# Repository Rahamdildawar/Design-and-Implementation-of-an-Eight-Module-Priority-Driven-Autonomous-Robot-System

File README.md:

# 🤖 Eight-Module Priority-Driven Autonomous Robot System

**Design and Implementation of an Eight-Module Priority-Driven Autonomous Robot System with Integrated Computer Vision and Multi-Sensor Fusion**

Author: **Raham Dil** — Computer Engineering, Ghulam Ishaq Khan Institute of Engineering Sciences and Technology (GIKI)
📧 u2024529@giki.edu.pk

<p align="center">
  <em>Platform: Arduino Mega 2560 + Python/OpenCV vision subsystem</em>
</p>

---

## 📖 Overview

This project presents a comprehensive **autonomous robot platform** built on the **Arduino Mega 2560**, augmented with a **laptop-based computer vision subsystem** written in **Python 3.9+ / OpenCV**. Eight independent hardware and software modules are unified under a **deterministic, five-level priority engine** that guarantees safe, predictable arbitration whenever multiple sensor events occur simultaneously (e.g., smoke detection + manual override + obstacle in path).

The system was validated experimentally, achieving **100% correct priority arbitration** across all tested concurrent-hazard scenarios.

---

## ✨ Key Contributions

- A **five-level priority engine** that deterministically arbitrates eight heterogeneous sensor-actuator modules in real time.
- An integrated **computer vision pipeline** (pothole detection, face dataset collection, gesture navigation zone) communicating with the embedded controller over a lightweight serial protocol.
- A **modular firmware/software architecture** enabling independent development and testing of each module while preserving system-wide safety invariants.
- **Empirical validation** of the priority engine under concurrent hazard conditions, with quantitative performance metrics.

---

## 🧩 System Modules

<table>
  <thead>
    <tr>
      <th align="center">#</th>
      <th align="left">Module</th>
      <th align="left">Description</th>
    </tr>
  </thead>
  <tbody>
    <tr>
      <td align="center">1</td>
      <td><strong>Smoke &amp; Gas Detection</strong></td>
      <td>3× MQ-series gas sensors (L/C/R) — highest priority safety shutdown</td>
    </tr>
    <tr>
      <td align="center">2</td>
      <td><strong>Pothole Detection (CV)</strong></td>
      <td>OpenCV pipeline: Gaussian blur → Canny edges → contour/circularity filtering</td>
    </tr>
    <tr>
      <td align="center">3</td>
      <td><strong>Flame Tracking &amp; Suppression</strong></td>
      <td>3× KY-026 IR flame sensors, 2-stage track-then-suppress logic with fan actuator</td>
    </tr>
    <tr>
      <td align="center">4</td>
      <td><strong>Ultrasonic Obstacle Avoidance</strong></td>
      <td>3× HC-SR04 sensors, reverse–scan–turn maneuver below 18 cm</td>
    </tr>
    <tr>
      <td align="center">5</td>
      <td><strong>Face Dataset Collection</strong></td>
      <td>Viola–Jones (Haar cascade) face capture pipeline for downstream recognition training</td>
    </tr>
    <tr>
      <td align="center">6</td>
      <td><strong>Finger Gesture Control</strong></td>
      <td>ROI-based gesture navigation zone (ready for MediaPipe Hands integration)</td>
    </tr>
    <tr>
      <td align="center">7</td>
      <td><strong>Bluetooth Teleoperation</strong></td>
      <td>HC-05 module on <code>Serial1</code>, ASCII motion + speed protocol</td>
    </tr>
    <tr>
      <td align="center">8</td>
      <td><strong>Infrared Line Following</strong></td>
      <td>5× TCRT5000 sensors, rule-based sensor-to-action mapping (default behavior)</td>
    </tr>
  </tbody>
</table>

<p align="center"><em>Representative component images (5-ch IR array, HC-SR04, L298N driver) — not the project's own hardware photos.</em></p>

---

## 🏗️ System Architecture

The software stack is split into two tiers:

- **Embedded tier (C++/Arduino):** Runs at ~200 Hz on the Mega 2560. Implements the priority engine, all sensor drivers, and motor control primitives.
- **Vision tier (Python 3.9+):** Runs on a connected laptop at ~25–30 FPS. Implements Modules 2, 5, and 6 via OpenCV, sending single-byte ASCII decisions to the embedded tier over USB serial.

```
┌─────────────────────────┐        USB Serial (9600 baud)        ┌──────────────────────────┐
│   Python Vision Tier     │ ────────────────────────────────────▶│   Arduino Mega 2560       │
│  (OpenCV, 25–30 FPS)     │   ASCII tokens: P, C, F, B, L, R, S   │  Priority Engine (~200Hz) │
│  • Pothole Detection     │◀──────────────────────────────────── │  • 8 Modules              │
│  • Face Collector        │                                       │  • Motor Control (L298N)  │
│  • Gesture Zone          │                                       └──────────────┬───────────┘
└─────────────────────────┘                                                       │ Serial1 (9600 baud)
                                                                                    ▼
                                                                        ┌──────────────────────┐
                                                                        │   HC-05 Bluetooth     │
                                                                        │   (Teleoperation)     │
                                                                        └──────────────────────┘
```

### Priority Hierarchy

<table>
  <thead>
    <tr>
      <th align="center">Priority</th>
      <th align="left">Condition</th>
      <th align="center">Modules</th>
      <th align="left">Action</th>
    </tr>
  </thead>
  <tbody>
    <tr>
      <td align="center"><strong>1 (highest)</strong></td>
      <td>Smoke OR pothole brake</td>
      <td align="center">1, 2</td>
      <td>Stop motors, buzzer ON, return</td>
    </tr>
    <tr>
      <td align="center"><strong>2</strong></td>
      <td>Flame detected</td>
      <td align="center">3</td>
      <td>Track &amp; suppress, return</td>
    </tr>
    <tr>
      <td align="center"><strong>3</strong></td>
      <td>Front obstacle &lt; 18 cm</td>
      <td align="center">4</td>
      <td>Reverse, scan, turn, return</td>
    </tr>
    <tr>
      <td align="center"><strong>4</strong></td>
      <td>Manual command within 700 ms</td>
      <td align="center">5, 6, 7</td>
      <td>Execute motion command, return</td>
    </tr>
    <tr>
      <td align="center"><strong>5 (default)</strong></td>
      <td>—</td>
      <td align="center">8</td>
      <td>Line following</td>
    </tr>
  </tbody>
</table>

Each level acts as a guard: if satisfied, all lower levels are bypassed via an early `return`, guaranteeing mutually exclusive behavior within a single control loop iteration.

---

## 🔌 Serial Communication Protocol

<table>
  <thead>
    <tr>
      <th align="center">Token</th>
      <th align="center">Direction</th>
      <th align="left">Meaning</th>
    </tr>
  </thead>
  <tbody>
    <tr><td align="center"><code>P</code></td><td align="center">PC → Mega</td><td>Pothole/hazard detected — halt</td></tr>
    <tr><td align="center"><code>C</code></td><td align="center">PC → Mega</td><td>Pothole cleared — resume</td></tr>
    <tr><td align="center"><code>F</code></td><td align="center">PC/BT → Mega</td><td>Move forward</td></tr>
    <tr><td align="center"><code>B</code></td><td align="center">PC/BT → Mega</td><td>Move backward</td></tr>
    <tr><td align="center"><code>L</code></td><td align="center">PC/BT → Mega</td><td>Pivot left</td></tr>
    <tr><td align="center"><code>R</code></td><td align="center">PC/BT → Mega</td><td>Pivot right</td></tr>
    <tr><td align="center"><code>S</code></td><td align="center">PC/BT → Mega</td><td>Stop motors</td></tr>
    <tr><td align="center"><code>0</code>–<code>9</code></td><td align="center">BT → Mega</td><td>Set speed (mapped 0–255)</td></tr>
  </tbody>
</table>

---

## 🛠️ Hardware / Pin Assignments (Arduino Mega 2560)

<table>
  <thead>
    <tr>
      <th align="left">Module</th>
      <th align="left">Signal</th>
      <th align="center">Pin</th>
      <th align="center">Direction</th>
    </tr>
  </thead>
  <tbody>
    <tr><td>Motor Driver</td><td>ENA / IN1 / IN2 / IN3 / IN4 / ENB</td><td align="center">2 / 3 / 4 / 7 / 8 / 5</td><td align="center">OUT</td></tr>
    <tr><td>Module 8 (Line)</td><td>S1–S5</td><td align="center">22–26</td><td align="center">IN</td></tr>
    <tr><td>Module 3 (Flame)</td><td>FL, FC, FR</td><td align="center">30–32</td><td align="center">IN</td></tr>
    <tr><td>Module 1 (Smoke)</td><td>SL, SC, SR</td><td align="center">35–37</td><td align="center">IN</td></tr>
    <tr><td>Module 4 (Ultrasonic)</td><td>TRIG/ECHO × 3</td><td align="center">40–45</td><td align="center">OUT/IN</td></tr>
    <tr><td>Actuators</td><td>FAN / BUZZER</td><td align="center">9 / 10</td><td align="center">OUT</td></tr>
  </tbody>
</table>

> Full wiring schematics, PCB layout (2D & 3D), and simulation screenshots (flame/smoke, line follower, Bluetooth, full-integration) are available in [`/docs/circuit-diagrams`](./docs/circuit-diagrams) — see the original report's Figure 2 set.

---

## 💻 Software Structure

**Embedded Firmware (`/firmware`)**
```
firmware/
├── main.ino                  # setup(), main priority-engine loop
├── serial_handler.cpp        # readControlInputs()
├── ultrasonic.cpp            # getDistance()
├── line_follower.cpp         # runLineFollowingRoutine()
├── manual_dispatch.cpp       # executeManualAction()
└── motor_primitives.cpp      # forward(), backward(), pivotLeft/Right(), stopMotors()
```

**Vision System (`/vision`)**
```
vision/
├── config.py           # Config dataclass — tunable parameters
├── serial_manager.py   # SerialManager — pyserial wrapper w/ simulation fallback
├── obstacle_detector.py# ObstacleDetector — Module 2 (pothole detection)
├── face_collector.py   # FaceCollector — Module 5
├── gesture_zone.py     # GestureZone — Module 6 ROI overlay/accessor
├── hud.py              # HUD — on-screen status bar
└── main.py             # Entry point / frame processing loop
```

---

## 🚀 Getting Started

### Prerequisites
- Arduino IDE (or PlatformIO)
- Python 3.9+
- `opencv-python`, `pyserial` (`pip install opencv-python pyserial`)
- Arduino Mega 2560, L298N driver, HC-SR04 ×3, KY-026 ×3, MQ-series gas sensors ×3, TCRT5000 ×5, HC-05

### 1. Flash the firmware
```bash
# Open firmware/main.ino in Arduino IDE, select "Arduino Mega 2560", and upload
```

### 2. Run the vision system
```bash
cd vision
python main.py --port COM5 --baud 9600   # adjust port for your OS
```

### 3. Control the robot
- **Autonomous:** line following runs by default; hazards auto-preempt.
- **Manual (Bluetooth/keyboard):** send `F`, `B`, `L`, `R`, `S`, or a digit `0`–`9` for speed.

---

## 📊 Experimental Results

### Priority Engine Arbitration (20 trials/scenario)

<table>
  <thead>
    <tr>
      <th align="left">Scenario</th>
      <th align="center">Expected</th>
      <th align="center">Observed</th>
      <th align="center">Accuracy</th>
    </tr>
  </thead>
  <tbody>
    <tr><td>Smoke only</td><td align="center">Stop+Buzz</td><td align="center">Stop+Buzz</td><td align="center">100%</td></tr>
    <tr><td>Flame only</td><td align="center">Track+Fan</td><td align="center">Track+Fan</td><td align="center">100%</td></tr>
    <tr><td>Obstacle only</td><td align="center">Avoid</td><td align="center">Avoid</td><td align="center">100%</td></tr>
    <tr><td>Smoke + Flame</td><td align="center">Stop+Buzz</td><td align="center">Stop+Buzz</td><td align="center">100%</td></tr>
    <tr><td>Smoke + Manual</td><td align="center">Stop+Buzz</td><td align="center">Stop+Buzz</td><td align="center">100%</td></tr>
    <tr><td>Flame + Manual</td><td align="center">Track+Fan</td><td align="center">Track+Fan</td><td align="center">100%</td></tr>
    <tr><td>Pothole (CV) + Manual</td><td align="center">Stop</td><td align="center">Stop</td><td align="center">100%</td></tr>
    <tr><td>All hazards active</td><td align="center">Stop+Buzz</td><td align="center">Stop+Buzz</td><td align="center">100%</td></tr>
  </tbody>
</table>

100% correct arbitration was observed across all 8 concurrent hazard scenarios.

### Pothole Detection (Module 2) — Confusion Matrix (200-frame test set)

<table>
  <thead>
    <tr>
      <th></th>
      <th align="center">Predicted: Pothole</th>
      <th align="center">Predicted: Clear</th>
      <th align="center">Total</th>
    </tr>
  </thead>
  <tbody>
    <tr><td><strong>Actual: Pothole</strong></td><td align="center">88</td><td align="center">12</td><td align="center">100</td></tr>
    <tr><td><strong>Actual: Clear</strong></td><td align="center">9</td><td align="center">91</td><td align="center">100</td></tr>
    <tr><td><strong>Total</strong></td><td align="center">97</td><td align="center">103</td><td align="center">200</td></tr>
  </tbody>
</table>

<table>
  <thead>
    <tr><th align="left">Metric</th><th align="center">Value</th></tr>
  </thead>
  <tbody>
    <tr><td>Precision</td><td align="center">90.7%</td></tr>
    <tr><td>Recall</td><td align="center">88.0%</td></tr>
    <tr><td>F1-Score</td><td align="center">0.894</td></tr>
  </tbody>
</table>

### Obstacle Avoidance (Module 4) — Threshold 18 cm

<table>
  <thead>
    <tr>
      <th align="center">Distance (cm)</th>
      <th align="center">Trials</th>
      <th align="center">Detected</th>
      <th align="center">Avoided</th>
      <th align="center">Accuracy</th>
    </tr>
  </thead>
  <tbody>
    <tr><td align="center">10</td><td align="center">10</td><td align="center">10</td><td align="center">10</td><td align="center">100%</td></tr>
    <tr><td align="center">15</td><td align="center">10</td><td align="center">10</td><td align="center">10</td><td align="center">100%</td></tr>
    <tr><td align="center">20</td><td align="center">10</td><td align="center">0</td><td align="center">0</td><td align="center">N/A</td></tr>
    <tr><td align="center">25</td><td align="center">10</td><td align="center">0</td><td align="center">0</td><td align="center">N/A</td></tr>
  </tbody>
</table>

### Line Following (Module 8)

<table>
  <thead>
    <tr>
      <th align="left">Track Type</th>
      <th align="center">Laps</th>
      <th align="center">Completed</th>
      <th align="center">Rate</th>
    </tr>
  </thead>
  <tbody>
    <tr><td>Straight</td><td align="center">10</td><td align="center">10</td><td align="center">100%</td></tr>
    <tr><td>Gentle curve (15°)</td><td align="center">10</td><td align="center">10</td><td align="center">100%</td></tr>
    <tr><td>Sharp curve (45°)</td><td align="center">10</td><td align="center">8</td><td align="center">80%</td></tr>
  </tbody>
</table>

### End-to-End Latency (Pothole Detection → Motor Stop, 50 trials)

<table>
  <thead>
    <tr><th align="left">Metric</th><th align="center">Value</th></tr>
  </thead>
  <tbody>
    <tr><td>Mean latency</td><td align="center">48.3 ms</td></tr>
    <tr><td>Standard deviation</td><td align="center">6.1 ms</td></tr>
    <tr><td>Maximum latency</td><td align="center">62 ms</td></tr>
  </tbody>
</table>

Dominant cost: USB-UART transmission at 9600 baud + camera frame period (~33 ms at 30 fps).

---

## ⚠️ Known Limitations

- **Blocking delays** in flame suppression (2 s) and obstacle avoidance (350/500 ms) pause serial processing — future work: interrupt/timer-driven non-blocking control.
- **Pothole detector** (classical CV) is sensitive to lighting; a lightweight CNN (e.g., MobileNetV2) is recommended for outdoor robustness.
- **Gesture recognition (Module 6)** currently only renders the ROI — classifier (e.g., MediaPipe Hands) not yet implemented.
- **Serial protocol** has no checksum/error correction; a lightweight XOR checksum is a suggested improvement.

---

## 🔭 Future Work

- Replace blocking delays with timer-interrupt–based non-blocking suppression/avoidance routines.
- Integrate a CNN-based pothole detector.
- Implement the Module 6 gesture classifier (MediaPipe Hands or custom CNN).
- Add a lightweight serial error-detection/checksum scheme.
- Increase baud rate to 115200 to reduce end-to-end latency.

---

## 📚 References

Key references include Brooks' subsumption architecture, Arkin's motor-schema navigation, Siegwart & Nourbakhsh's *Introduction to Autonomous Mobile Robots*, Viola & Jones' cascade face detector, and ROS (Quigley et al.). See the full report for the complete bibliography.

---

## 🙏 Acknowledgment

Thanks to the Department of Electrical Engineering (GIKI) for providing laboratory facilities and hardware components used in this project.

---

## 📄 License

This project is released for educational and research purposes. Add your preferred license (e.g., MIT) here.

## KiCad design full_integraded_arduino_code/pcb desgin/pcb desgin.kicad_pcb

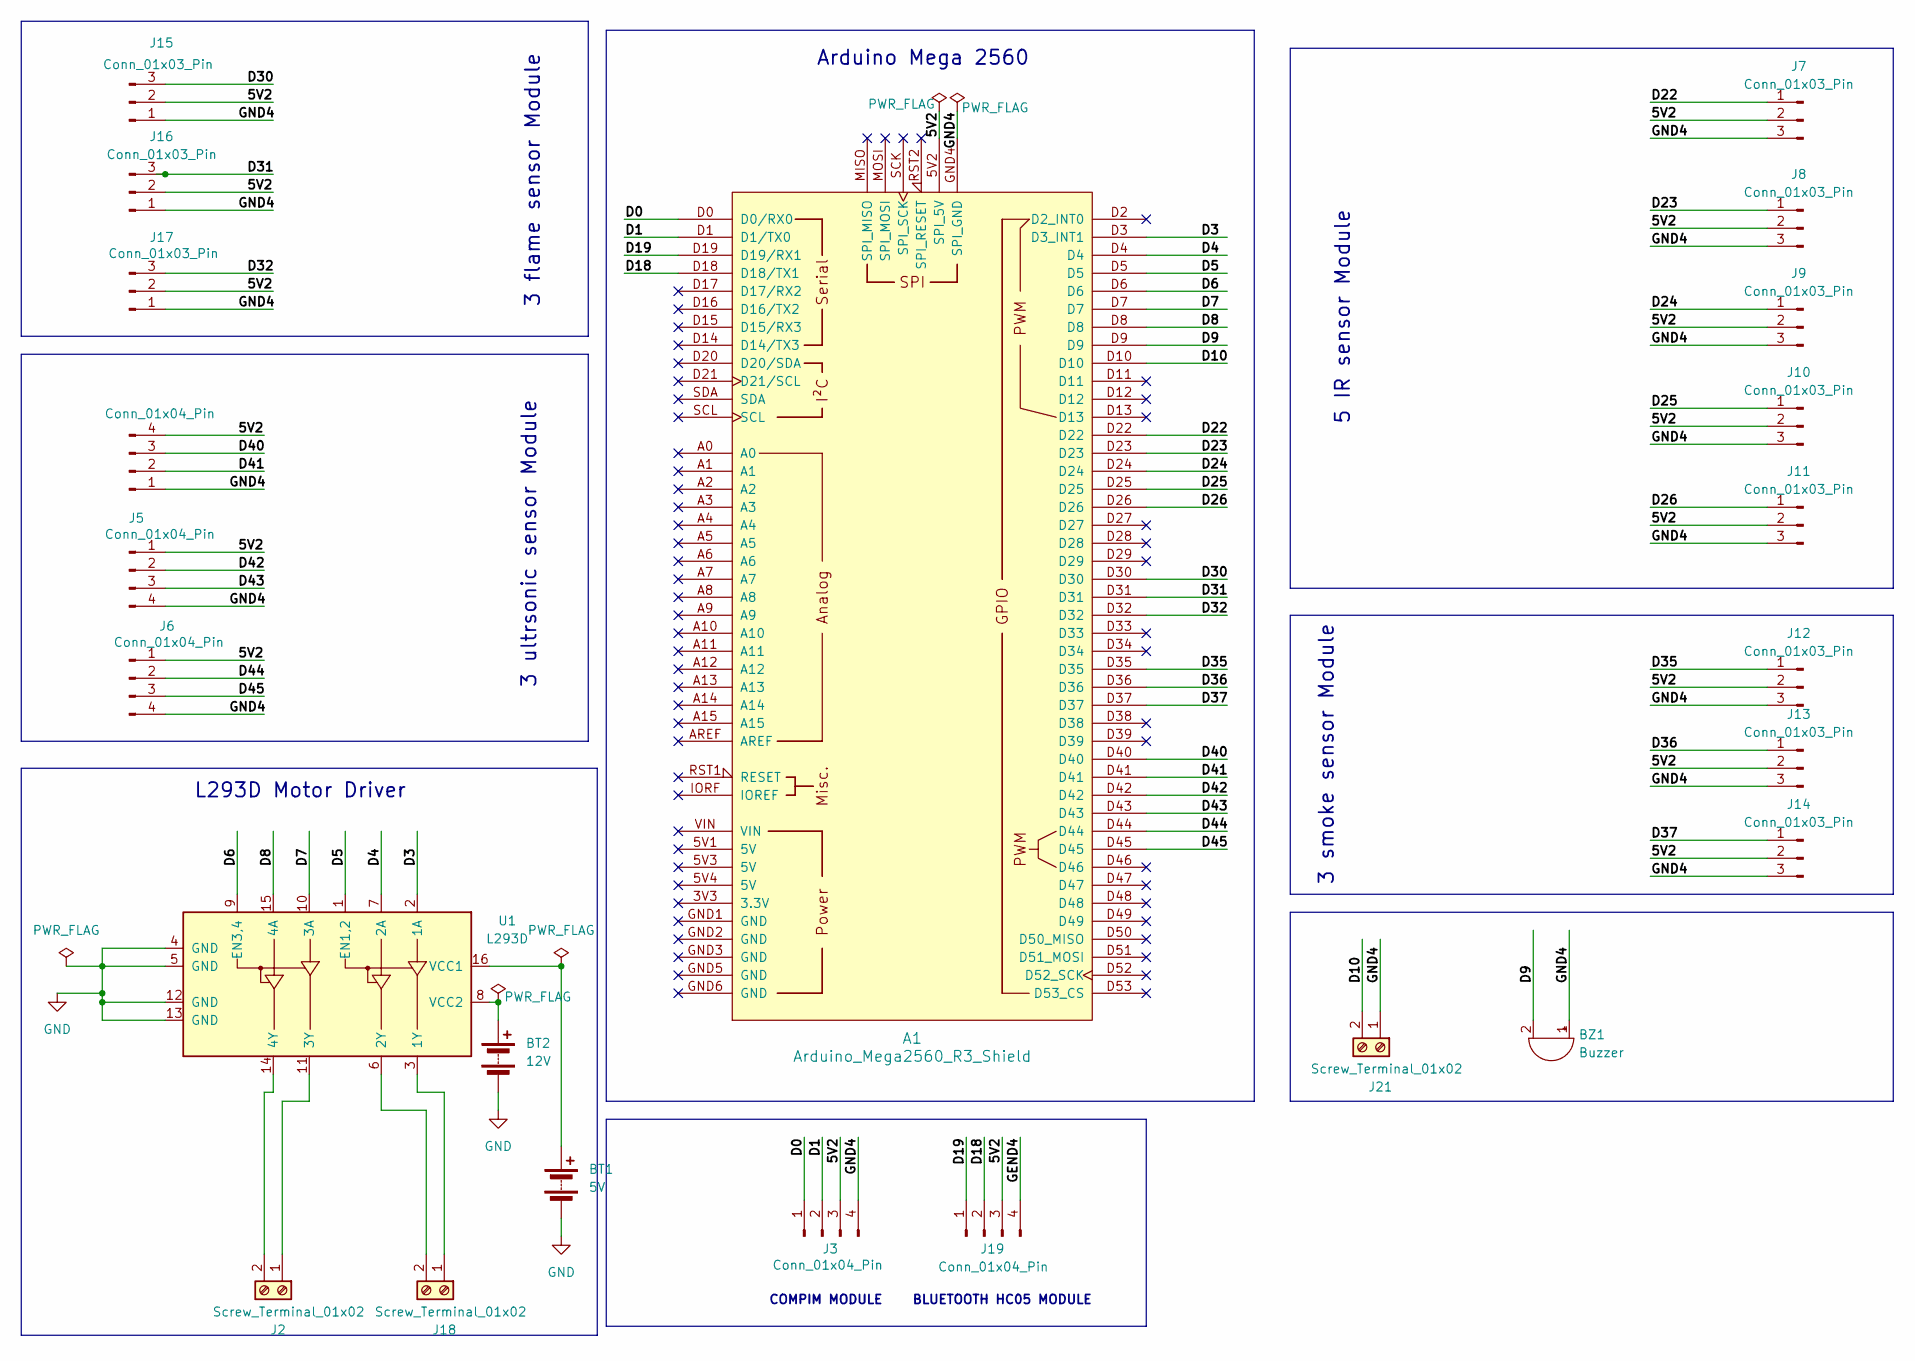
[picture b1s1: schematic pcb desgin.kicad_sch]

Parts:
A1: Arduino_Mega2560_R3_Shield; Clone_Mega2560_Pro_Socket
BT1: 5V; TerminalBlock_MaiXu_MX126-5.0-02P_1x02_P5.00mm
BT2: 12V; TerminalBlock_MaiXu_MX126-5.0-02P_1x02_P5.00mm
BZ1: Buzzer; Buzzer_TDK_PS1240P02BT_D12.2mm_H6.5mm
J2, J18, J21: Screw_Terminal_01x02; TerminalBlock_Xinya_XY308-2.54-2P_1x02_P2.54mm_Horizontal
J3, J4, J5, J6, J19: Conn_01x04_Pin; PinHeader_1x04_P2.54mm_Horizontal
J7, J8, J9, J10, J11, J12, J13, J14, J15, J16, J17: Conn_01x03_Pin; PinHeader_1x03_P2.54mm_Horizontal
U1: L293D; DIP-16_W7.62mm

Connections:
/5V2: A1.5V2 (SPI_5V), J3.3, J4.4, J5.1, J6.1, J7.2, J8.2, J9.2, J10.2, J11.2, J12.2, J13.2, J14.2, J15.2, J16.2, J17.2, J19.3
/D0: A1.D0 (D0/RX0), J3.1
/D1: A1.D1 (D1/TX0), J3.2
/D3: A1.D3 (D3_INT1), U1.2 (1A)
/D4: A1.D4, U1.7 (2A)
/D5: A1.D5, U1.1 (EN1,2)
/D6: A1.D6, U1.9 (EN3,4)
/D7: A1.D7, U1.10 (3A)
/D8: A1.D8, U1.15 (4A)
/D9: A1.D9, BZ1.2 (-)
/D10: A1.D10, J21.2
/D18: A1.D18 (D18/TX1), J19.2
/D19: A1.D19 (D19/RX1), J19.1
/D22: A1.D22, J7.1
/D23: A1.D23, J8.1
/D24: A1.D24, J9.1
/D25: A1.D25, J10.1
/D26: A1.D26, J11.1
/D30: A1.D30, J15.3
/D31: A1.D31, J16.3
/D32: A1.D32, J17.3
/D35: A1.D35, J12.1
/D36: A1.D36, J13.1
/D37: A1.D37, J14.1
/D40: A1.D40, J4.3
/D41: A1.D41, J4.2
/D42: A1.D42, J5.2
/D43: A1.D43, J5.3
/D44: A1.D44, J6.2
/D45: A1.D45, J6.3
/GEND4: J19.4
/GND4: A1.GND4 (SPI_GND), BZ1.1 (+), J3.4, J4.1, J5.4, J6.4, J7.3, J8.3, J9.3, J10.3, J11.3, J12.3, J13.3, J14.3, J15.1, J16.1, J17.1, J21.1
GND: BT1.2 (-), BT2.2 (-), U1.4 (GND), U1.5 (GND), U1.12 (GND), U1.13 (GND)
unnamed: BT1.1 (+), U1.16 (VCC1)
unnamed: BT2.1 (+), U1.8 (VCC2)
unnamed: J2.1, U1.11 (3Y)
unnamed: J2.2, U1.14 (4Y)
unnamed: J18.1, U1.3 (1Y)
unnamed: J18.2, U1.6 (2Y)

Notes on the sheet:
COMPIM MODULE
5 IR sensor Module
3 flame sensor Module
BLUETOOTH HC05 MODULE
L293D Motor Driver
3 smoke sensor Module
3 ultrsonic sensor Module
Arduino Mega 2560

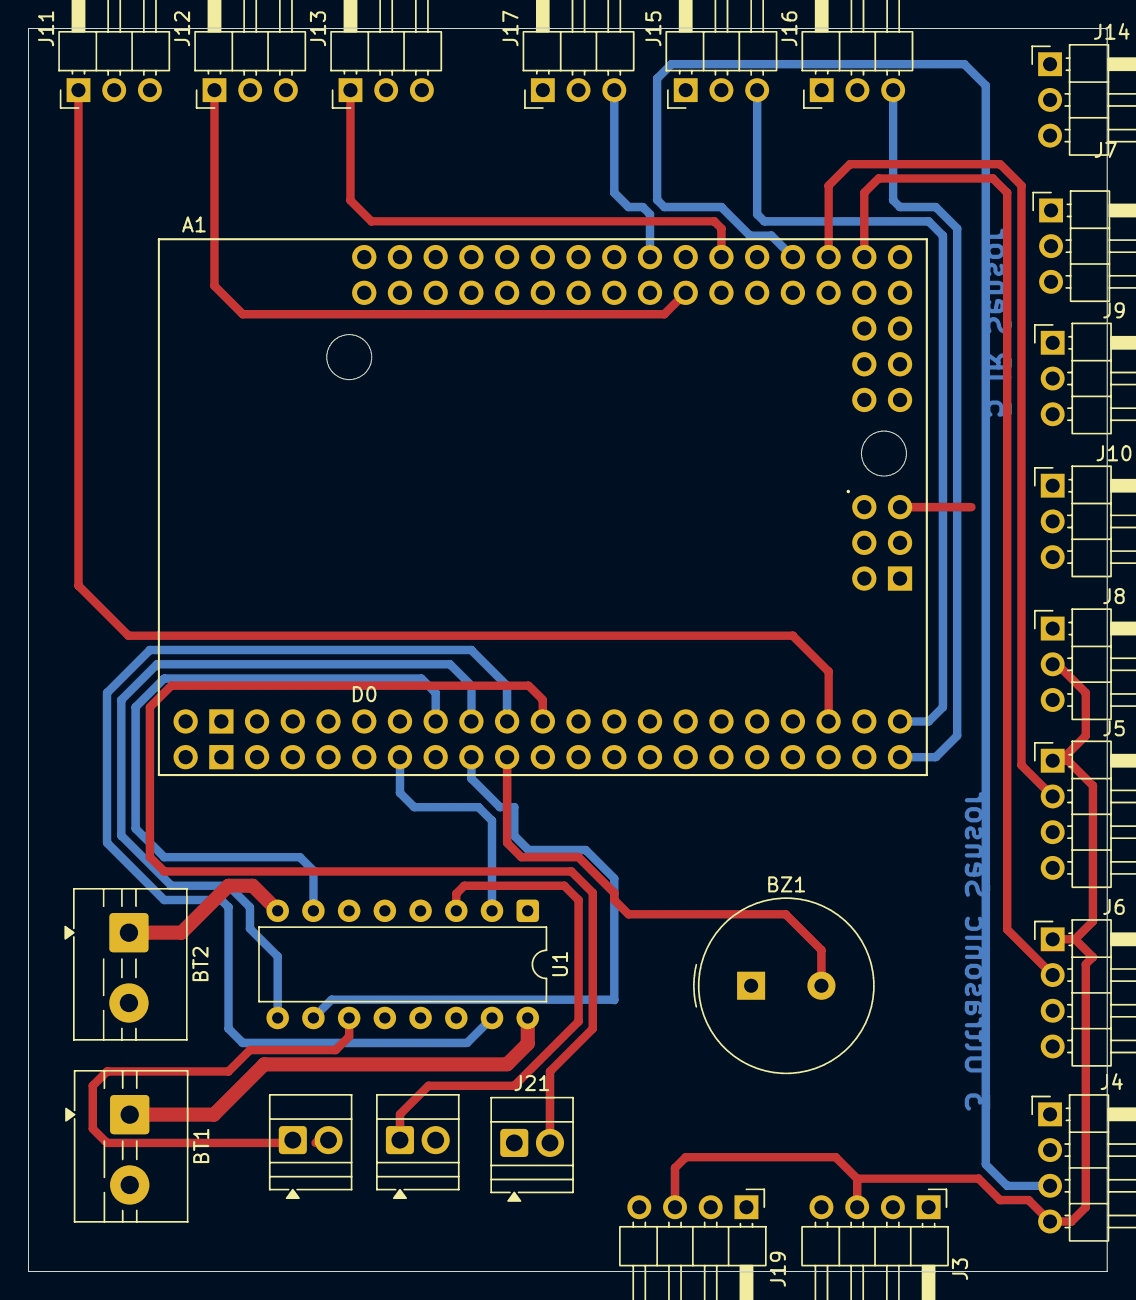
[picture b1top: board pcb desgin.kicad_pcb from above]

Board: 4 copper layers, 76.7 x 88.4 mm, 24 parts (0 on the bottom side), 38 nets.
